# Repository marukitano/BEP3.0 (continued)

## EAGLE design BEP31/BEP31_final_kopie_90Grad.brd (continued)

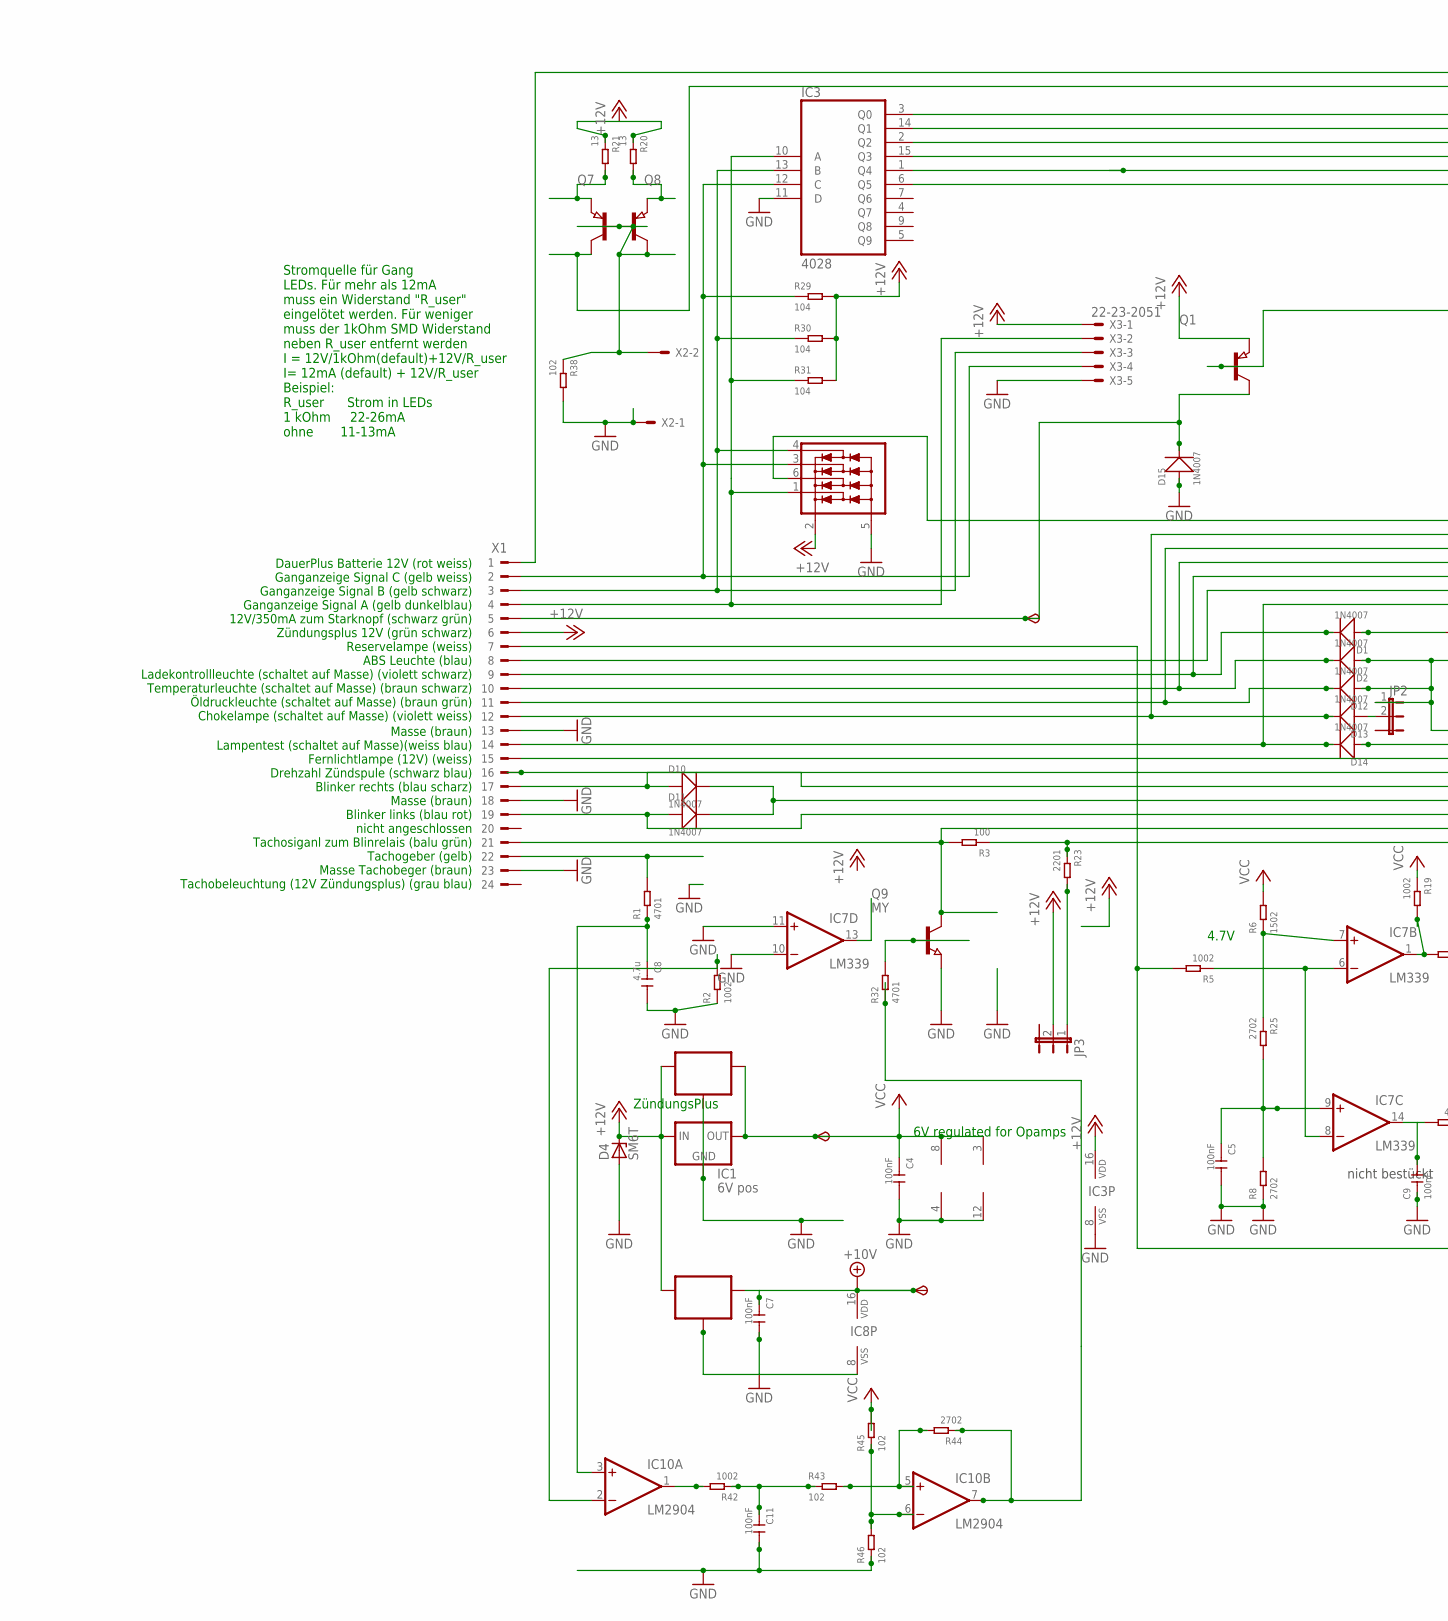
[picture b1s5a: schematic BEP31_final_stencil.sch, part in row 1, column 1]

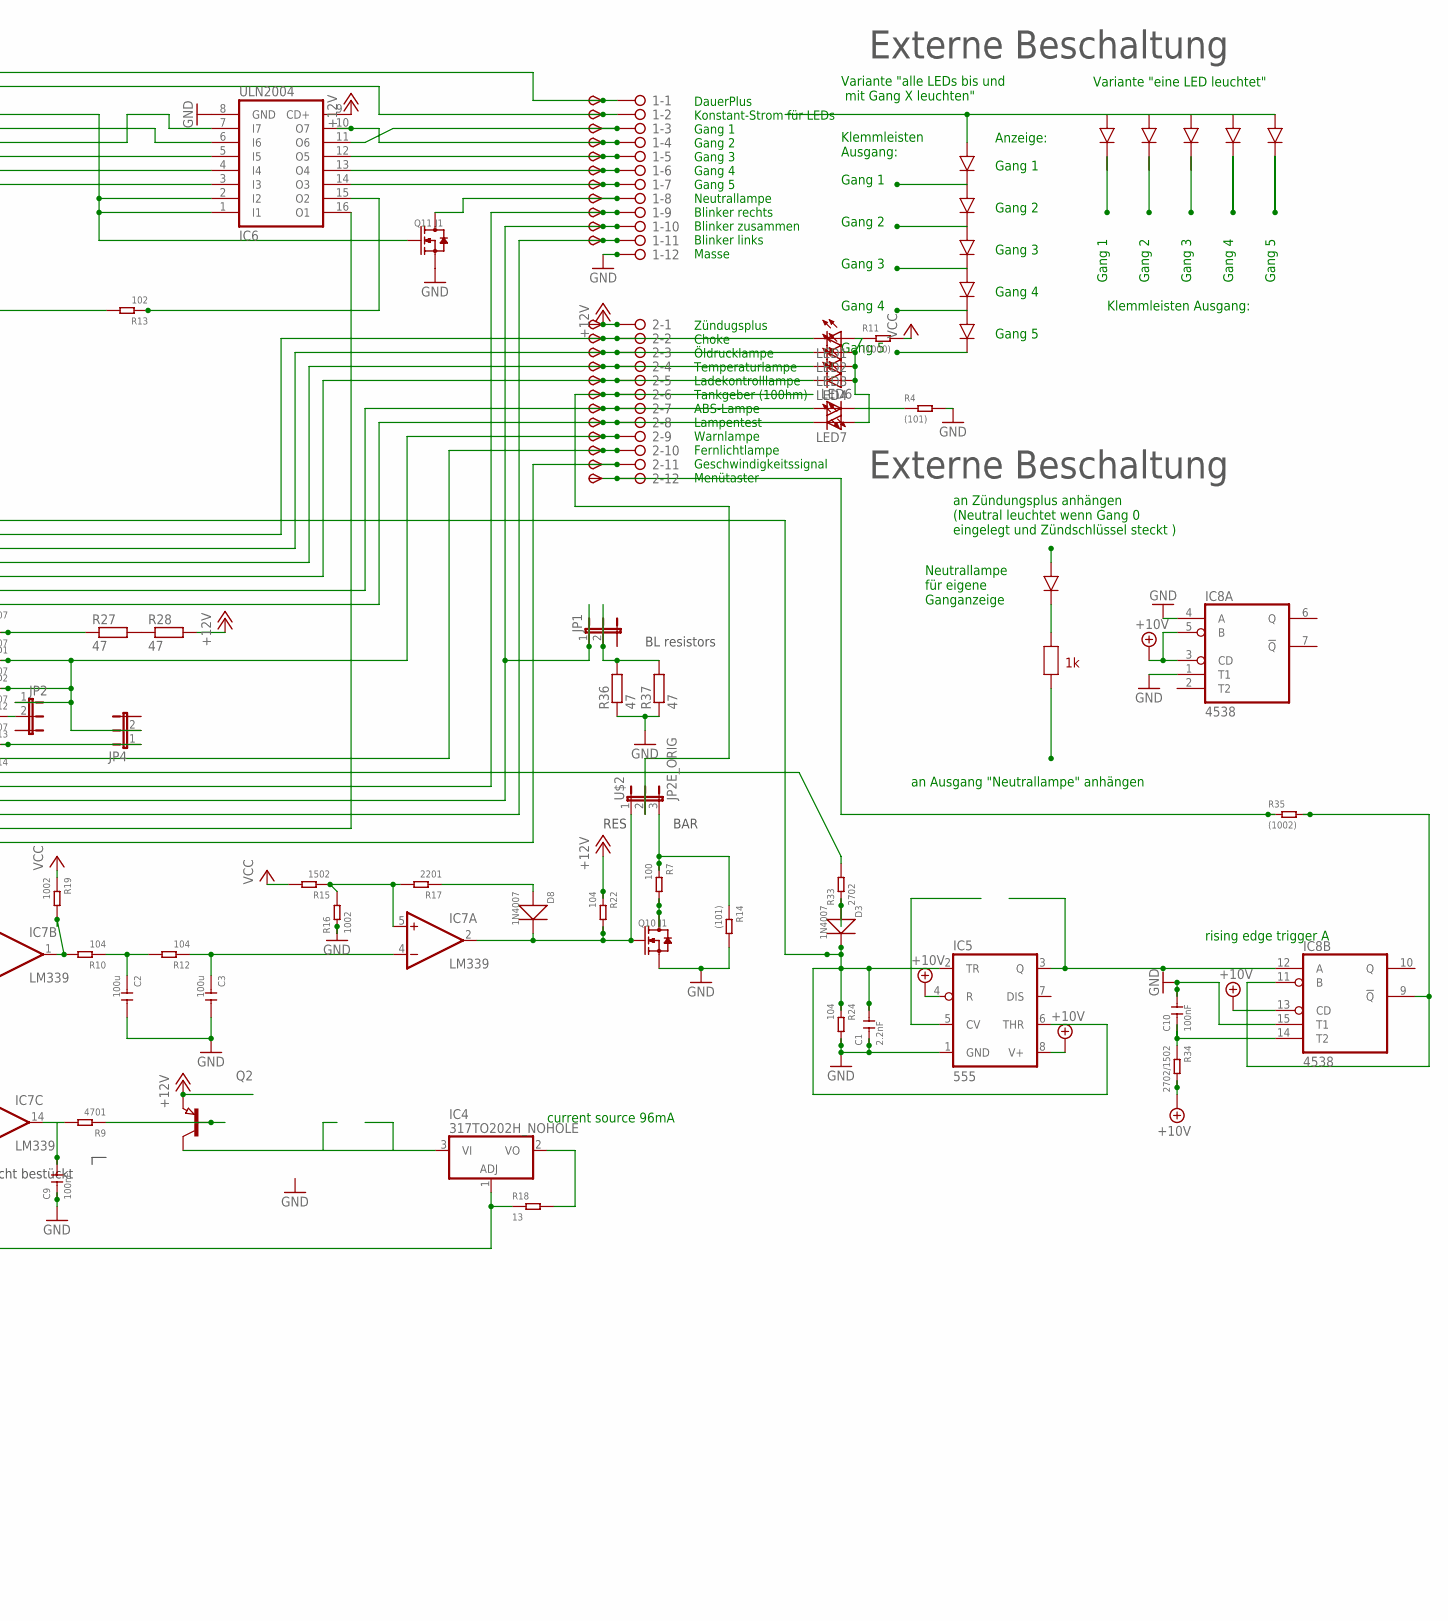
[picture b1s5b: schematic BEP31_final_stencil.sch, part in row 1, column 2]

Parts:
1, 2: 2081-1132; 12-PIN
6V, 10V: TPSB2.0; B2.0
C1: 2.2nF; C0805
C2, C3: 100u; C1206
C4, C5, C7, C9, C10, C11: 100nF; C0805
C8: 4.7u; C0805
D1, D3, D8, D10, D11, D15: 1N4007; DO-214AC
D2, D12, D13, D14: 1N4007; DO-214AC-1206MOUNT
D4: SM6T; DO214AA
IC1: 6V pos; 78LXX
IC2, IC9: 78LXXSOT89_ROUND; SOT89_ROUND
IC3: 4028; SO16
IC4: 317TO202H_NOHOLE; TO220H_NOHOLE
IC5: 555; SO08
IC6: ULN2004; SO16
IC7: LM339; SO14
IC8: 4538; SO16
IC10: LM2904; SO08
JP1, JP2, JP3, JP4: JP2EJP2_SMALLPADS; JP2_SMALLPADS
LED1, LED2, LED3, LED4, LED6, LED7: LEDLD260; LD260
Q1, Q2, Q7, Q8: PNP-TRANSISTOR_SOT89; SOT89
Q9: MY; SOT89
Q10, Q11: J1; SOT-23
R1, R9, R32: 4701; R0805
R2, R5, R16, R19, R42: 1002; R0805
R3, R7: 100; R0805
R4, R14: (101); R0805
R6, R15: 1502; R0805
R8, R25, R33, R44: 2702; R0805
R10, R12, R22, R24, R29, R30, R31: 104; R0805
R11: (1000); R0805
R13, R38, R43, R45, R46: 102; R0805
R17, R23: 2201; R0805
R18, R20, R21: 13; R1206
R27, R28, R36, R37: 47; V235/17_1MM
R34: 2702/1502; R0805
R35: (1002); R0805
START: TPSB2.0; B2.0
TP1, TP2, TP3, TP4, TP5, TP6, TP7, TP8, TP9, TP10, TP11, TP12, TP13, TP16, TP17, TP18, TP19, TP21, TP22, TP23, TP25, TP26: TPSB2.0; B2.0
TP24: TPSB1,27; B1,27
U$2: JP2E_ORIG; JP2_ORIG_SMALLPADS
U$3: NUP4304SOT457_R; SOT457R_PHILIPS
X1: CON_BMWV2; 24-PIN_V2
X2: 22-23-2021
X3: 22-23-2051

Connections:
+10V: 10V.TP, C7.1, IC5.4 (R), IC5.8 (V+), IC8.3 (CD), IC8.5 (B), IC8.13 (CD), IC8.16 (VDD), IC9.1 (OUT), R34.2
+12V: 2.1, D4.C, IC1.IN, IC2.3 (IN), IC3.16 (VDD), IC6.9 (CD+), IC9.3 (IN), JP3.2, Q1.3 (E), Q2.3 (E), R20.1, R21.1, R22.1, R28.2, R29.2, R30.2, R31.2, TP12.TP, U$3.2 (V+), X1.6, X3.1; also elsewhere on the board
+12V1: IC10.7 (OUT), R32.1, R44.1
GND: 1.12, C1.1, C2.2, C3.2, C4.2, C5.2, C7.2, C8.2, C9.1, C10.2, C11.2, D4.A, D15.1 (+), IC1.GND, IC2.2 (GND), IC2.2@1 (GND), IC3.8 (VSS), IC3.11 (D), IC5.1 (GND), IC6.8 (GND), IC7.10 (-IN), IC7.11 (+IN), IC7.12 (GND), IC8.1 (T1), IC8.4 (A), IC8.8 (VSS), IC8.15 (T1), IC9.2 (GND), IC9.2@1 (GND), IC10.4 (V-), Q9.3 (E), Q10.2 (S), Q11.2 (S), R2.1, R4.2, R8.1, R14.2, R16.1, R24.2, R36.1, R37.1, R38.2, R46.1, U$3.5 (V-), X1.13, X1.18, X1.23, X2.1, X3.5; also elsewhere on the board
unnamed: 2.9, D2.1 (+), D12.1 (+), JP2.1, JP4.2, TP24.TP
unnamed: IC3.10 (A), R31.1, U$3.1 (D1), X1.4, X3.2
unnamed: IC3.13 (B), R30.1, U$3.4 (D4), X1.3, X3.3
unnamed: 2.7, LED6.A, TP22.TP, X1.8
unnamed 8: Q8.3 (E), R21.2; also elsewhere on the board
unnamed: D8.2 (-), IC7.2 (OUT), Q10.1 (G), R22.2, U$2.1
unnamed: IC10.2 (-IN), R2.2
unnamed: R27.2, R28.1
unnamed 12: Q7.3 (E), R20.2; also elsewhere on the board
unnamed 14: D15.2 (-), Q1.2 (C), START.TP, X1.5; also elsewhere on the board
unnamed: 2.2, D13.2 (-), LED1.K (C), TP16.TP, X1.12
unnamed: 2.3, D12.2 (-), LED2.K (C), TP17.TP, X1.11
unnamed: 2.4, D2.2 (-), LED3.K (C), TP18.TP, X1.10
unnamed 18: IC4.3 (VI), Q2.2 (C); also elsewhere on the board
unnamed: IC7.6 (-IN), IC7.8 (-IN), R5.1
unnamed: IC3.12 (C), R29.1, U$3.3 (D3), X1.2, X3.4
unnamed: IC3.15 (Q3), IC6.5 (I5)
unnamed: 2.8, D14.2 (-), LED7.K (C), TP23.TP, X1.14
unnamed: 1.9, D10.1 (+), TP9.TP, X1.17
unnamed: 1.11, D11.1 (+), TP11.TP, X1.19
unnamed: IC8.9 (!Q), IC8.11 (B), R35.2
unnamed 26: R1.2, X1.22; also elsewhere on the board
unnamed: C8.1, IC10.3 (+IN), R1.1
unnamed: 1.6, IC6.13 (O4), TP6.TP
unnamed: 1.7, IC6.14 (O3), TP7.TP
unnamed: 2.11, R3.1, R23.1, TP26.TP
unnamed: 2.6, TP21.TP, U$2.2
unnamed: JP3.1, R23.2
unnamed: C5.1, IC7.9 (+IN), R8.2, R25.2
unnamed: C9.2, IC7.14 (OUT), R9.2
unnamed: C1.2, D3.2 (-), IC5.2 (TR), IC5.6 (THR), R24.1, U$3.6 (D2)
unnamed: LED6.K (C), R4.1
unnamed: IC4.1 (ADJ), R5.2, R18.1, X1.7
unnamed 39: Q2.1 (B), R9.1; also elsewhere on the board
unnamed: IC3.2 (Q2), IC6.7 (I7)
unnamed: 1.3, IC6.11 (O6), TP3.TP
unnamed: 1.5, IC6.12 (O5), TP5.TP
unnamed: LED1.A, LED2.A, LED3.A, LED4.A, LED7.A, R11.1
unnamed: R33.2, X1.16
unnamed 46: Q1.1 (B), R13.2; also elsewhere on the board
unnamed: IC3.3 (Q0), IC6.1 (I1), IC6.2 (I2), Q11.1 (G)
unnamed: C2.1, R10.1, R12.2
unnamed: C3.1, IC7.4 (-IN), R12.1
unnamed: IC7.5 (+IN), R15.1, R16.2, R17.2
unnamed: Q10.3 (D), R7.2
unnamed: D8.1 (+), R17.1
unnamed: IC3.1 (Q4), IC6.4 (I4)
unnamed: 1.8, Q11.3 (D), TP8.TP
unnamed: 2.10, TP25.TP, X1.15
unnamed: D1.1 (+), R27.1
unnamed: 2.5, D1.2 (-), LED4.K (C), TP19.TP, X1.9
unnamed: IC3.14 (Q1), IC6.6 (I6)
unnamed 59: Q7.1 (B), Q7.2 (C), Q8.1 (B), R38.1, X2.2; also elsewhere on the board
unnamed 60: 1.2, Q8.2 (C), TP2.TP; also elsewhere on the board
unnamed: IC3.6 (Q5), IC6.3 (I3)
unnamed: IC4.2 (VO), R18.2
unnamed 66: IC5.5 (CV); also elsewhere on the board
unnamed: 1.4, IC6.10 (O7), TP4.TP
unnamed: 1.1, TP1.TP, X1.1
unnamed: IC7.7 (+IN), R6.1, R25.1
unnamed 75: IC6.16 (O1), Q9.2 (C), R3.2, X1.21; also elsewhere on the board
unnamed 76: Q9.1 (B), R32.2; also elsewhere on the board
unnamed 77: IC5.3 (Q), IC8.12 (A); also elsewhere on the board
unnamed: D3.1 (+), R33.1
unnamed: IC6.15 (O2), R13.1
unnamed: C10.1, IC8.14 (T2), R34.1
unnamed: 2.12, R35.1, TP13.TP
unnamed: IC10.1 (OUT), R42.2
unnamed 83: 1.10, D10.2 (-), D11.2 (-), JP1.1, TP10.TP; also elsewhere on the board
unnamed 84: JP1.2, R36.2, R37.2; also elsewhere on the board
unnamed: D13.1 (+), JP2.2
unnamed: C11.1, R42.1, R43.1
unnamed: IC10.5 (+IN), R43.2, R44.2
unnamed: D14.1 (+), JP4.1
unnamed: R7.1, R14.1, U$2.3
unnamed: IC10.6 (-IN), R45.1, R46.2
unnamed: IC7.1 (OUT), R10.2, R19.2
VCC: 6V.TP, C4.1, IC1.OUT, IC2.1 (OUT), IC7.3 (V+), IC10.8 (V+), R6.2, R11.2, R15.2, R19.1, R45.2

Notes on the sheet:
6V regulated for Opamps
current source 96mA
ZündungsPlus
Zündugsplus Choke Öldrucklampe Temperaturlampe Ladekontrolllampe Tankgeber (100hm) ABS-Lampe Lampentest Warnlampe Fernlichtlampe Geschwindigkeitssignal Menütaster
DauerPlus Konstant-Strom für LEDs Gang 1 Gang 2 Gang 3 Gang 4 Gang 5 Neutrallampe Blinker rechts Blinker zusammen Blinker links Masse
DauerPlus Batterie 12V (rot weiss) Ganganzeige Signal C (gelb weiss) Ganganzeige Signal B (gelb schwarz) Ganganzeige Signal A (gelb dunkelblau) 12V/350mA zum Starknopf (schwarz grün) Zündungsplus 12V (grün schwarz) Reservelampe (weiss) ABS Leuchte (blau) Ladekontrollleuchte (schaltet auf Masse) (vi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
Masse (braun) Lampentest (schaltet auf Masse)(weiss blau) Fernlichtlampe (12V) (weiss) Drehzahl Zündspule (schwarz blau) Blinker rechts (blau scharz) Masse (braun) Blinker links (blau rot) nicht angeschlossen Tachosiganl zum Blinrelais (balu grün) Tachogeber (gelb) Masse Tachobeger (braun) Tachobel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
4.7V
Stromquelle für Gang LEDs. Für mehr als 12mA muss ein Widerstand "R_user" eingelötet werden. Für weniger muss der 1kOhm SMD Widerstand neben R_user entfernt werden I = 12V/1kOhm(default)+12V/R_user I= 12mA (default) + 12V/R_user Beispiel: R_user Strom in LEDs 1 kOhm 22-26mA ohne 11-13mA
Gang 1
Gang 2
Gang 3
Gang 4
Gang 5
Variante "eine LED leuchtet"
Variante "alle LEDs bis und mit Gang X leuchten"
Klemmleisten Ausgang:
Klemmleisten Ausgang:
an Zündungsplus anhängen (Neutral leuchtet wenn Gang 0 eingelegt und Zündschlüssel steckt )
an Ausgang "Neutrallampe" anhängen
Neutrallampe für eigene Ganganzeige
Externe Beschaltung
Anzeige:
nicht bestückt
rising edge trigger A
BAR
RES
BL resistors

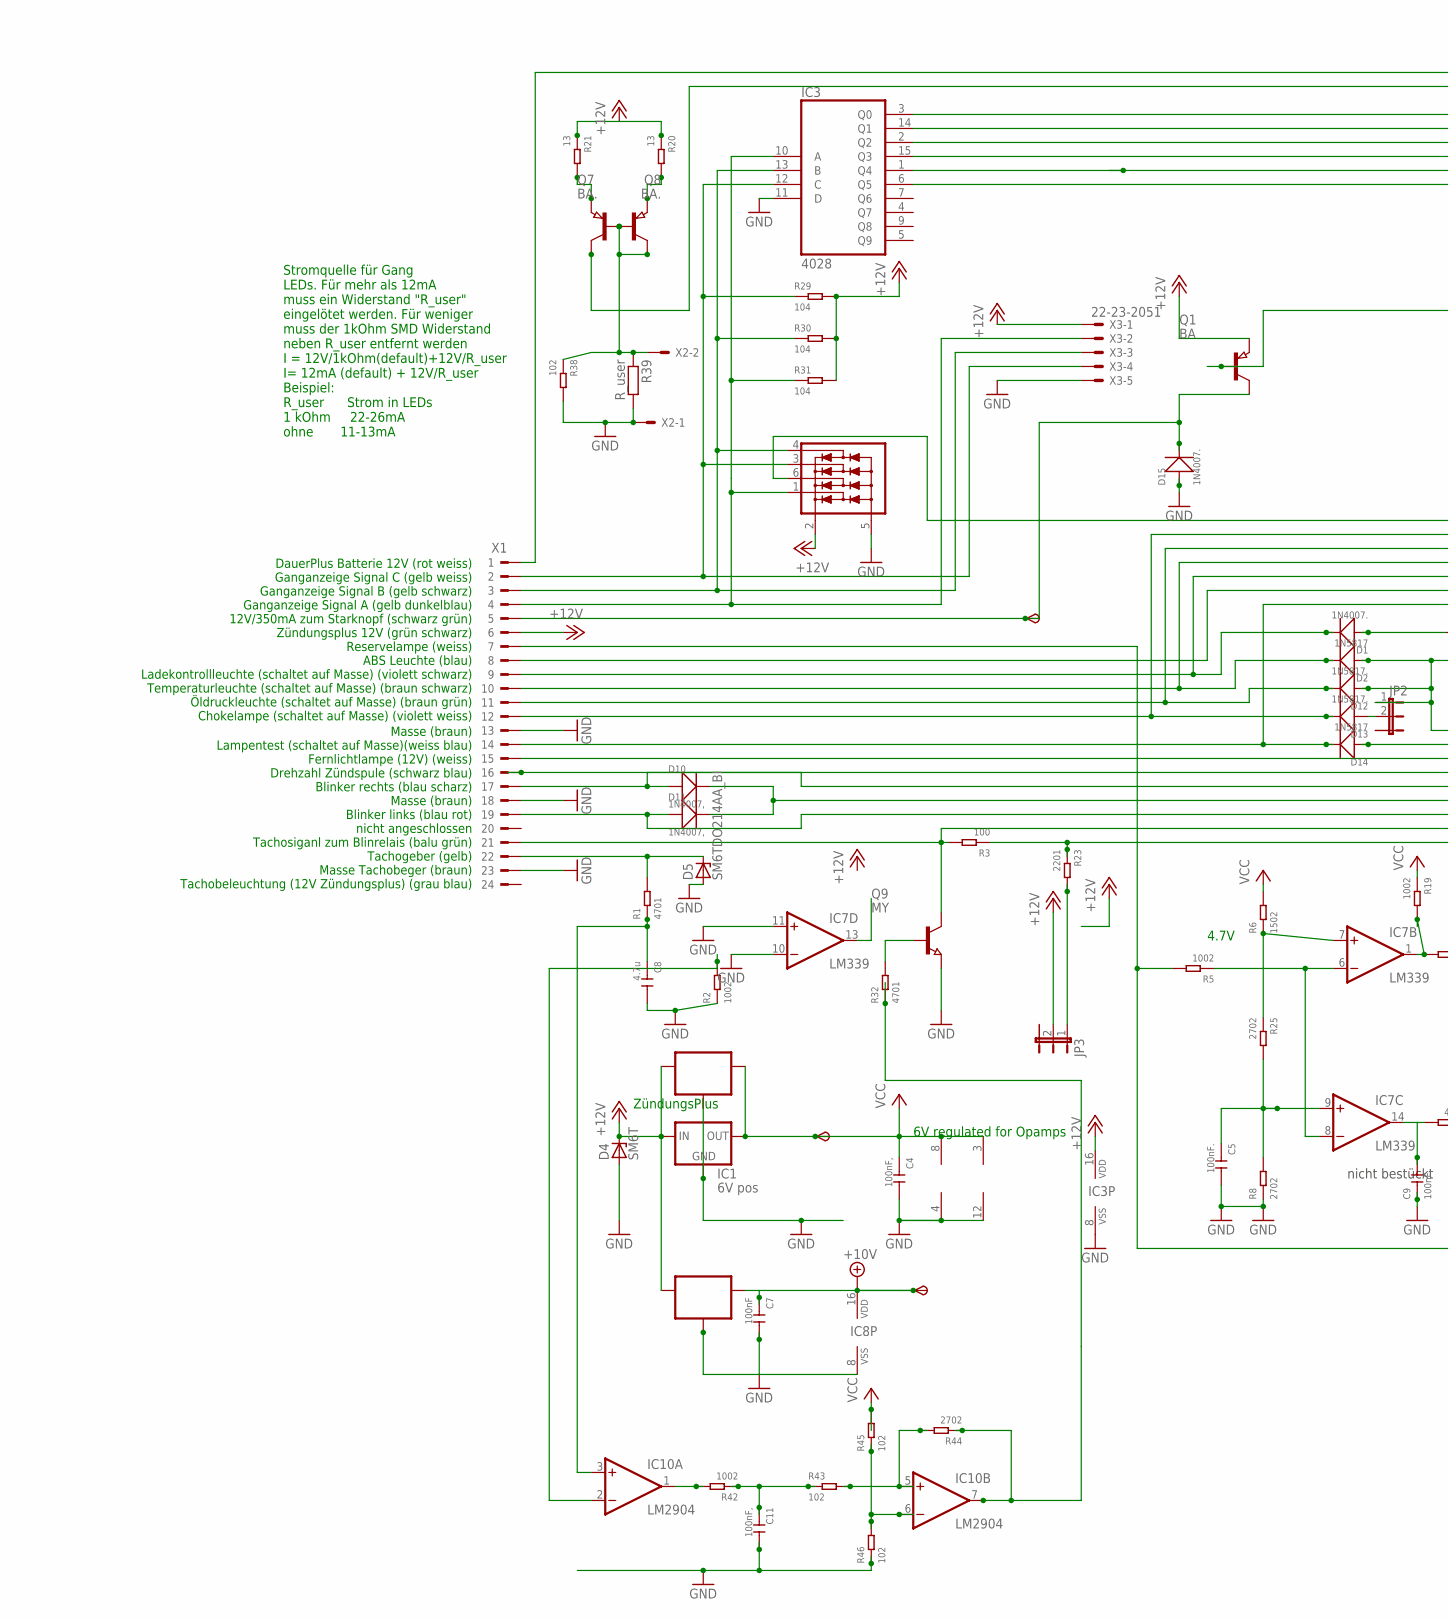
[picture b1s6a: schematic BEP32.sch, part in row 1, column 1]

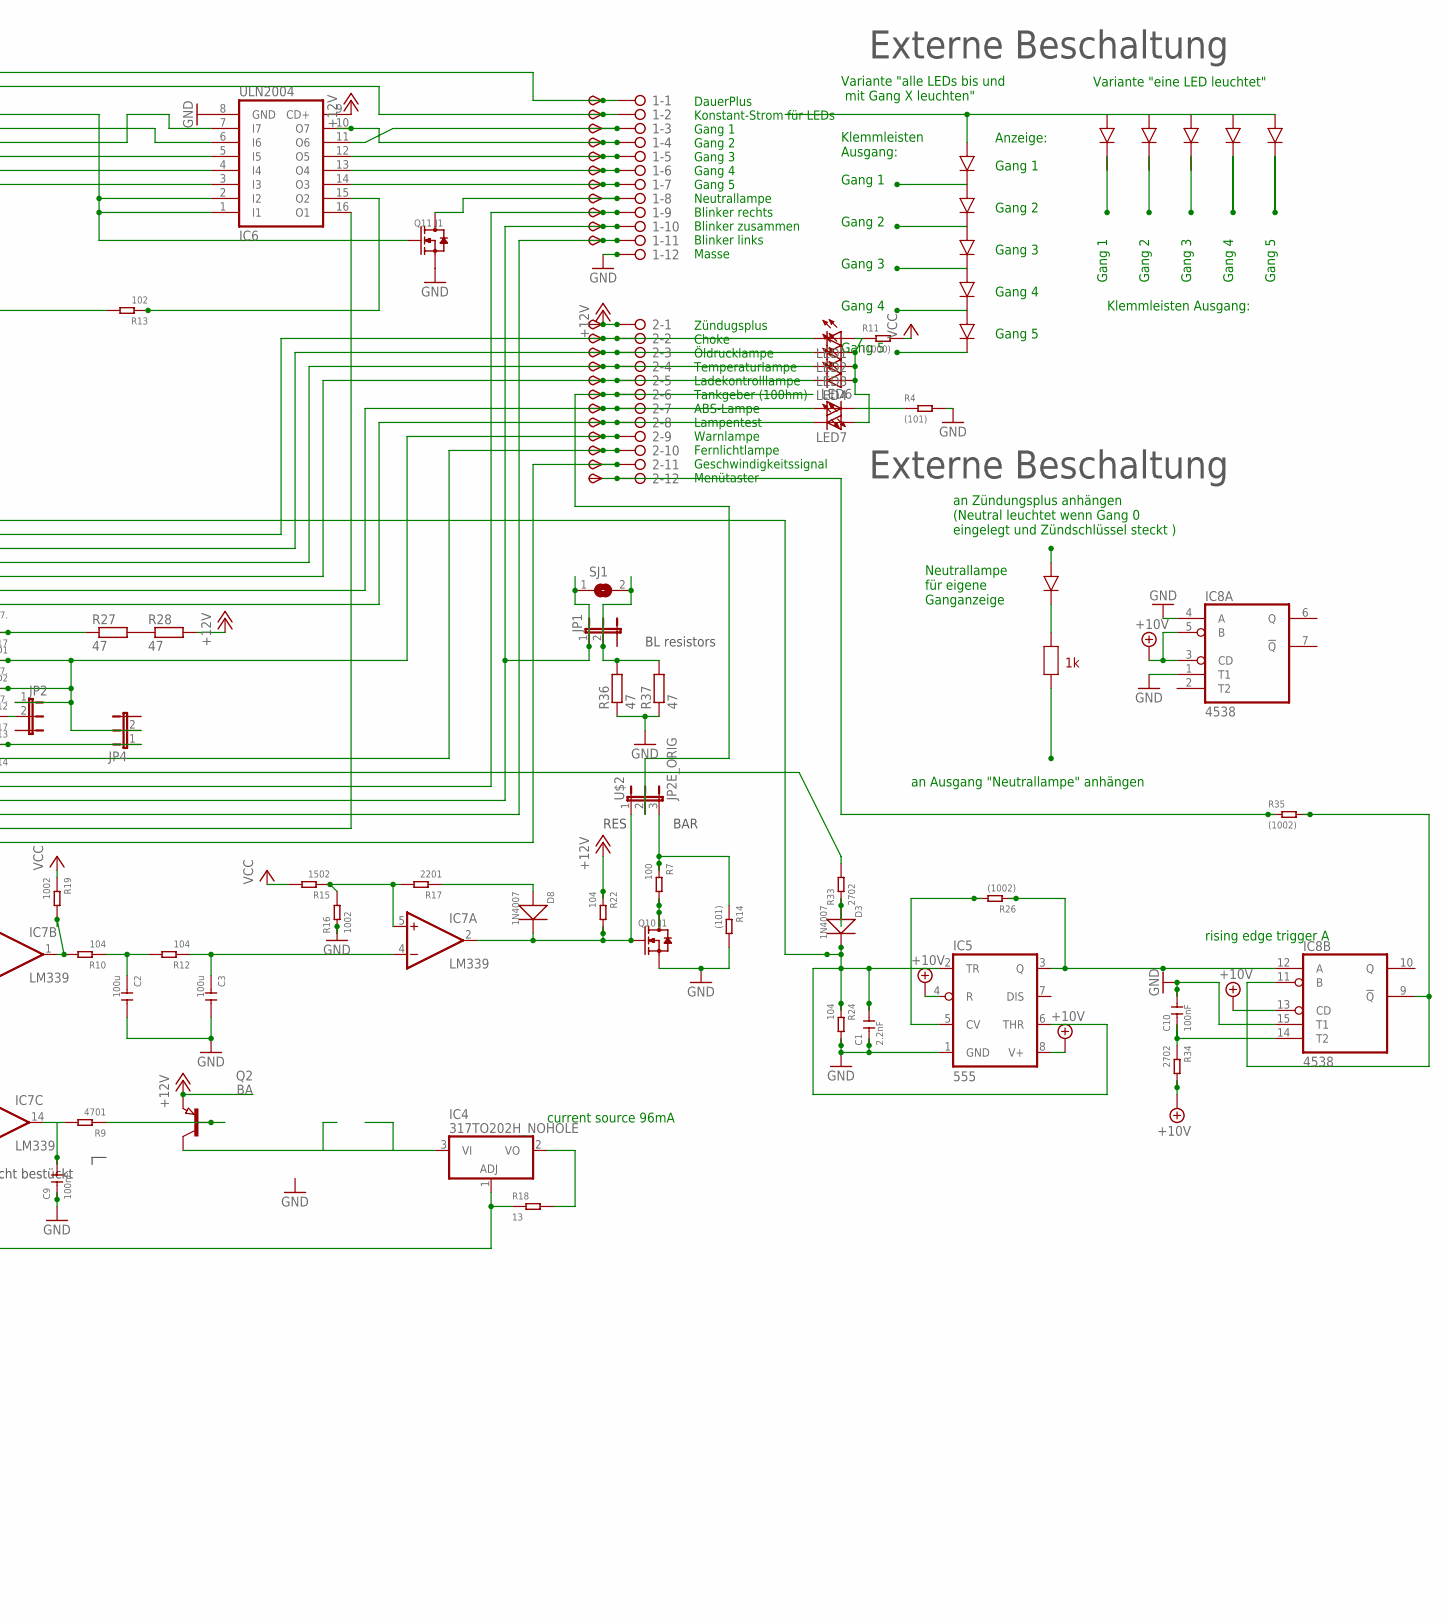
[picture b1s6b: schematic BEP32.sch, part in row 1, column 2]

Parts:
1, 2: 2081-1132; 12-PIN
6V, 10V: TPSB2.0; B2.0
C1: 2.2nF; C0805
C2, C3: 100u; C1206
C4, C11: 100nF,; C0805
C5, C9: 100nF.; C0805
C7, C10: 100nF; C0805
C8: 4.7u; C0805
D1, D15: 1N4007.; DO-214AC
D2, D14: 1N5817; DO-214AC_SLIM
D3, D8: 1N4007; DO-214AC
D4: SM6T; DO214AA
D5: SM6TDO214AA_BI; DO214AA_BI
D10, D11: 1N4007,; DO-214AC
D12, D13: 1N5817.; DO-214AC_SLIM
IC1: 6V pos; 78LXX
IC2: 78L06; SOT89_ROUND
IC3: 4028; SO16
IC4: 317TO202H_NOHOLE; TO220H_NOHOLE
IC5: 555; SO08
IC6: ULN2004; SO16
IC7: LM339; SO14
IC8: 4538; SO16
IC9: 78L10; SOT89_ROUND
IC10: LM2904; SO08
JP1, JP2, JP3, JP4: JP2EJP2_SMALLPADS; JP2_SMALLPADS
LED1, LED2, LED3, LED4, LED6, LED7: LEDLD260; LD260
Q1, Q2: BA; SOT89
Q7, Q8: BA.; SOT89
Q9: MY; SOT89
Q10, Q11: J1; SOT-23
R1, R9, R32: 4701; R0805
R2, R5, R16, R19, R42: 1002; R0805
R3, R7: 100; R0805
R4, R14: (101); R0805
R6, R15: 1502; R0805
R8, R25, R33, R34, R44: 2702; R0805
R10, R12, R22, R24, R29, R30, R31: 104; R0805
R11: (1000); R0805
R13, R38, R43, R45, R46: 102; R0805
R17, R23: 2201; R0805
R18, R20, R21: 13; R1206
R26, R35: (1002); R0805
R27, R28, R36, R37: 47; V235/17_1MM
R39: R_user; R0805
SJ1: SJ
START: TPSB2.0; B2.0
TP1, TP2, TP3, TP4, TP5, TP6, TP7, TP8, TP9, TP10, TP11, TP12, TP13, TP16, TP17, TP18, TP19, TP21, TP22, TP23, TP25, TP26: TPSB2.0; B2.0
TP24: TPSB1,27; B1,27
U$2: JP2E_ORIG; JP2_ORIG_SMALLPADS
U$3: NUP4304SOT457_R; SOT457R_PHILIPS
X1: CON_BMWV2; 24-PIN_V2
X2: 22-23-2021
X3: 22-23-2051

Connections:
+10V: 10V.TP, C7.1, IC5.4 (R), IC5.8 (V+), IC8.3 (CD), IC8.5 (B), IC8.13 (CD), IC8.16 (VDD), IC9.1 (OUT), R34.2
+12V: 2.1, D4.C, IC1.IN, IC2.3 (IN), IC3.16 (VDD), IC6.9 (CD+), IC9.3 (IN), JP3.2, Q1.3 (E), Q2.3 (E), R20.1, R21.1, R22.1, R28.2, R29.2, R30.2, R31.2, TP12.TP, U$3.2 (V+), X1.6, X3.1; also elsewhere on the board
+12V1: IC10.7 (OUT), R32.1, R44.1
GND: 1.12, C1.1, C2.2, C3.2, C4.2, C5.2, C7.2, C8.2, C9.1, C10.2, C11.2, D4.A, D5.A, D15.1 (+), IC1.GND, IC2.2 (GND), IC2.2@1 (GND), IC3.8 (VSS), IC3.11 (D), IC5.1 (GND), IC6.8 (GND), IC7.10 (-IN), IC7.11 (+IN), IC7.12 (GND), IC8.1 (T1), IC8.4 (A), IC8.8 (VSS), IC8.15 (T1), IC9.2 (GND), IC9.2@1 (GND), IC10.4 (V-), Q9.3 (E), Q10.2 (S), Q11.2 (S), R2.1, R4.2, R8.1, R14.2, R16.1, R24.2, R36.1, R37.1, R38.2, R39.2, R46.1, U$3.5 (V-), X1.13, X1.18, X1.23, X2.1, X3.5; also elsewhere on the board
unnamed: 2.9, D2.1 (+), D12.1 (+), JP2.1, JP4.2, TP24.TP
unnamed: IC3.10 (A), R31.1, U$3.1 (D1), X1.4, X3.2
unnamed: IC3.13 (B), R30.1, U$3.4 (D4), X1.3, X3.3
unnamed: 2.7, LED6.A, TP22.TP, X1.8
unnamed 8: Q8.3 (E), R21.2; also elsewhere on the board
unnamed: D8.2 (-), IC7.2 (OUT), Q10.1 (G), R22.2, U$2.1
unnamed: IC10.2 (-IN), R2.2
unnamed: R27.2, R28.1
unnamed 12: Q7.3 (E), R20.2; also elsewhere on the board
unnamed 14: D15.2 (-), Q1.2 (C), START.TP, X1.5; also elsewhere on the board
unnamed: 2.2, D13.2 (-), LED1.K (C), TP16.TP, X1.12
unnamed: 2.3, D12.2 (-), LED2.K (C), TP17.TP, X1.11
unnamed: 2.4, D2.2 (-), LED3.K (C), TP18.TP, X1.10
unnamed 18: IC4.3 (VI), Q2.2 (C); also elsewhere on the board
unnamed: IC7.6 (-IN), IC7.8 (-IN), R5.1
unnamed: IC3.12 (C), R29.1, U$3.3 (D3), X1.2, X3.4
unnamed: IC3.15 (Q3), IC6.5 (I5)
unnamed: 2.8, D14.2 (-), LED7.K (C), TP23.TP, X1.14
unnamed: 1.9, D10.1 (+), TP9.TP, X1.17
unnamed: 1.11, D11.1 (+), TP11.TP, X1.19
unnamed: IC8.9 (!Q), IC8.11 (B), R35.2
unnamed: D5.C, R1.2, X1.22
unnamed: C8.1, IC10.3 (+IN), R1.1
unnamed: 1.6, IC6.13 (O4), TP6.TP
unnamed: 1.7, IC6.14 (O3), TP7.TP
unnamed: 2.11, R3.1, R23.1, TP26.TP
unnamed: 2.6, TP21.TP, U$2.2
unnamed: JP3.1, R23.2
unnamed: C5.1, IC7.9 (+IN), R8.2, R25.2
unnamed: C9.2, IC7.14 (OUT), R9.2
unnamed: C1.2, D3.2 (-), IC5.2 (TR), IC5.6 (THR), R24.1, U$3.6 (D2)
unnamed: LED6.K (C), R4.1
unnamed: IC4.1 (ADJ), R5.2, R18.1, X1.7
unnamed 39: Q2.1 (B), R9.1; also elsewhere on the board
unnamed: IC3.2 (Q2), IC6.7 (I7)
unnamed: 1.3, IC6.11 (O6), TP3.TP
unnamed: 1.5, IC6.12 (O5), TP5.TP
unnamed: LED1.A, LED2.A, LED3.A, LED4.A, LED7.A, R11.1
unnamed: R33.2, X1.16
unnamed 46: Q1.1 (B), R13.2; also elsewhere on the board
unnamed: IC3.3 (Q0), IC6.1 (I1), IC6.2 (I2), Q11.1 (G)
unnamed: C2.1, R10.1, R12.2
unnamed: C3.1, IC7.4 (-IN), R12.1
unnamed: IC7.5 (+IN), R15.1, R16.2, R17.2
unnamed: Q10.3 (D), R7.2
unnamed: D8.1 (+), R17.1
unnamed: IC3.1 (Q4), IC6.4 (I4)
unnamed: 1.8, Q11.3 (D), TP8.TP
unnamed: 2.10, TP25.TP, X1.15
unnamed: D1.1 (+), R27.1
unnamed: 2.5, D1.2 (-), LED4.K (C), TP19.TP, X1.9
unnamed: IC3.14 (Q1), IC6.6 (I6)
unnamed 59: Q7.1 (B), Q7.2 (C), Q8.1 (B), R38.1, R39.1, X2.2; also elsewhere on the board
unnamed 60: 1.2, Q8.2 (C), TP2.TP; also elsewhere on the board
unnamed: IC3.6 (Q5), IC6.3 (I3)
unnamed: IC4.2 (VO), R18.2
unnamed: IC5.5 (CV), R26.2
unnamed: 1.4, IC6.10 (O7), TP4.TP
unnamed: 1.1, TP1.TP, X1.1
unnamed: IC7.7 (+IN), R6.1, R25.1
unnamed 75: IC6.16 (O1), Q9.2 (C), R3.2, X1.21; also elsewhere on the board
unnamed 76: Q9.1 (B), R32.2; also elsewhere on the board
unnamed: IC5.3 (Q), IC8.12 (A), R26.1
unnamed: D3.1 (+), R33.1
unnamed: IC6.15 (O2), R13.1
unnamed: C10.1, IC8.14 (T2), R34.1
unnamed: 2.12, R35.1, TP13.TP
unnamed: IC10.1 (OUT), R42.2
unnamed: 1.10, D10.2 (-), D11.2 (-), JP1.1, SJ1.1, TP10.TP
unnamed: JP1.2, R36.2, R37.2, SJ1.2
unnamed: D13.1 (+), JP2.2
unnamed: C11.1, R42.1, R43.1
unnamed: IC10.5 (+IN), R43.2, R44.2
unnamed: D14.1 (+), JP4.1
unnamed: R7.1, R14.1, U$2.3
unnamed: IC10.6 (-IN), R45.1, R46.2
unnamed: IC7.1 (OUT), R10.2, R19.2
VCC: 6V.TP, C4.1, IC1.OUT, IC2.1 (OUT), IC7.3 (V+), IC10.8 (V+), R6.2, R11.2, R15.2, R19.1, R45.2

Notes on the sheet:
6V regulated for Opamps
current source 96mA
ZündungsPlus
Zündugsplus Choke Öldrucklampe Temperaturlampe Ladekontrolllampe Tankgeber (100hm) ABS-Lampe Lampentest Warnlampe Fernlichtlampe Geschwindigkeitssignal Menütaster
DauerPlus Konstant-Strom für LEDs Gang 1 Gang 2 Gang 3 Gang 4 Gang 5 Neutrallampe Blinker rechts Blinker zusammen Blinker links Masse
DauerPlus Batterie 12V (rot weiss) Ganganzeige Signal C (gelb weiss) Ganganzeige Signal B (gelb schwarz) Ganganzeige Signal A (gelb dunkelblau) 12V/350mA zum Starknopf (schwarz grün) Zündungsplus 12V (grün schwarz) Reservelampe (weiss) ABS Leuchte (blau) Ladekontrollleuchte (schaltet auf Masse) (vi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
Masse (braun) Lampentest (schaltet auf Masse)(weiss blau) Fernlichtlampe (12V) (weiss) Drehzahl Zündspule (schwarz blau) Blinker rechts (blau scharz) Masse (braun) Blinker links (blau rot) nicht angeschlossen Tachosiganl zum Blinrelais (balu grün) Tachogeber (gelb) Masse Tachobeger (braun) Tachobel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
4.7V
Stromquelle für Gang LEDs. Für mehr als 12mA muss ein Widerstand "R_user" eingelötet werden. Für weniger muss der 1kOhm SMD Widerstand neben R_user entfernt werden I = 12V/1kOhm(default)+12V/R_user I= 12mA (default) + 12V/R_user Beispiel: R_user Strom in LEDs 1 kOhm 22-26mA ohne 11-13mA
Gang 1
Gang 2
Gang 3
Gang 4
Gang 5
Variante "eine LED leuchtet"
Variante "alle LEDs bis und mit Gang X leuchten"
Klemmleisten Ausgang:
Klemmleisten Ausgang:
an Zündungsplus anhängen (Neutral leuchtet wenn Gang 0 eingelegt und Zündschlüssel steckt )
an Ausgang "Neutrallampe" anhängen
Neutrallampe für eigene Ganganzeige
Externe Beschaltung
Anzeige:
nicht bestückt
rising edge trigger A
BAR
RES
BL resistors

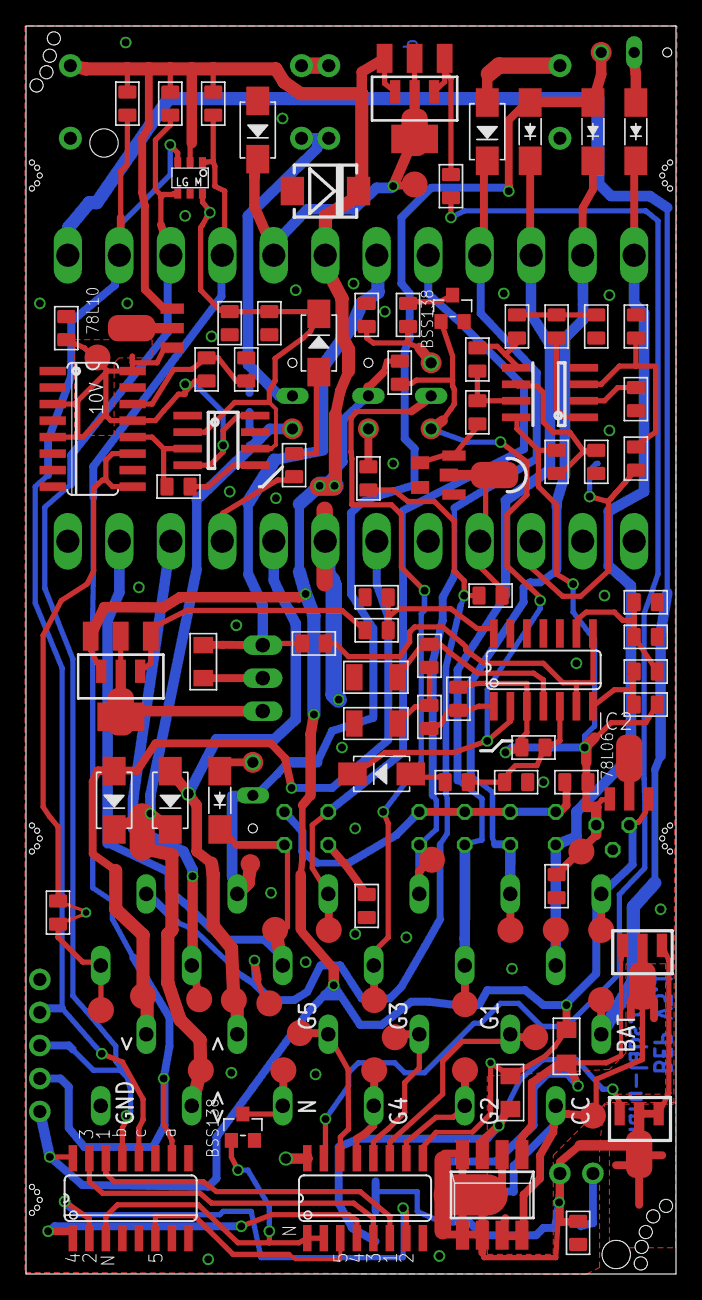
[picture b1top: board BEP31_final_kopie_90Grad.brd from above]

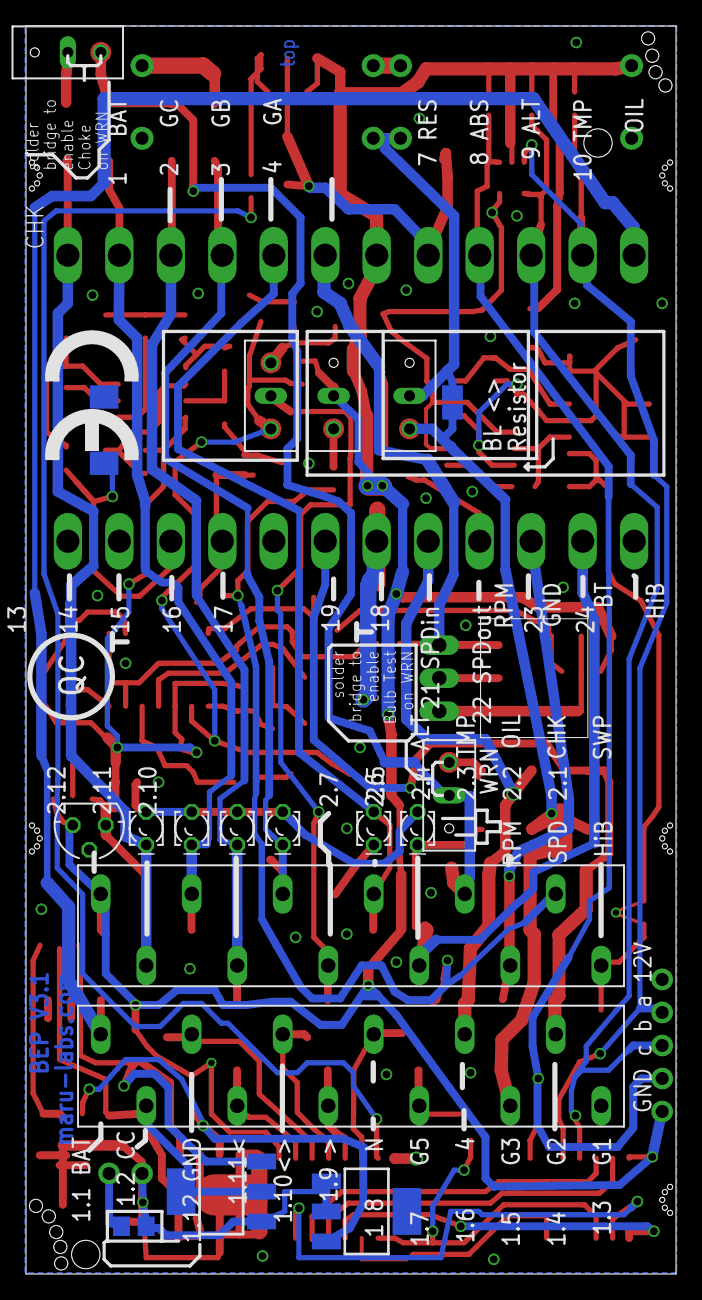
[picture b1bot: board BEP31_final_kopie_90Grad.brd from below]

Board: 2 copper layers, 50.0 x 96.0 mm, 136 parts (28 on the bottom side), 82 nets.

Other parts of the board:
FID1: FID1; ROUND_1.5MM_TPLACE
FID2: FID2; ROUND_1.5MM_TPLACE
U$1: CE_10.00

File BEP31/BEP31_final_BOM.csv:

"Qty";"Value";"Device";"Package";"Parts";"Description";"MF";"MPN";"OC_FARNELL";"OC_NEWARK";"TP";"TP_SIGNAL_NAME";"VALUE";
"2";"";"2081-1132";"12-PIN";"1, 2";"WAGO SREW CLAMP";"";"";"";"";"";"";"";
"2";"";"78LXXSOT89_ROUND";"SOT89_ROUND";"IC2, IC9";"";"";"";"";"";"";"";"";
"1";"";"CON_BMWV2";"24-PIN_V2";"X1";"BMW CONNECTOR";"";"";"";"";"";"";"";
"4";"";"JP2EJP2_SMALLPADS";"JP2_SMALLPADS";"JP1, JP2, JP3, JP4";"JUMPER";"";"";"";"";"";"";"";
"6";"";"LEDLD260";"LD260";"LED1, LED2, LED3, LED4, LED6, LED7";"LED";"";"";"";"";"";"";"";
"4";"";"PNP-TRANSISTOR_SOT89";"SOT89";"Q1, Q2, Q7, Q8";"PNP TRANSISTOR";"";"";"";"";"";"";"";
"1";"(1000)";"SMD-RES-100R-5%-1/8W(0805)";"R0805";"R11";"301010319";"";"RC0805JR-07100RL";"";"";"";"";"100R";
"1";"(1002)";"SMD-RES-4.7K-5%-1/8W(0805)";"R0805";"R35";"301010306";"";"RC0805JR-074K7L";"";"";"";"";"4.7K";
"1";"(101)";"SMD-RES-100R-5%-1/8W(0805)";"R0805";"R4";"301010319";"";"RC0805JR-07100RL";"";"";"";"";"100R";
"1";"(101)";"SMD-RES-2.2K-5%-1/8W(0805)";"R0805";"R14";"301010333";"";"RC0805JR-072K2L";"";"";"";"";"2.2K";
"1";"100";"SMD-RES-2.2K-5%-1/8W(0805)";"R0805";"R7";"301010333";"";"RC0805JR-072K2L";"";"";"";"";"2.2K";
"1";"100";"SMD-RES-220R-5%-1/8W(0805)";"R0805";"R3";"301010315";"";"RC0805JR-07220RL";"";"";"";"";"220R";
"5";"1002";"SMD-RES-10K-1%-1/8W(0805)";"R0805";"R2, R5, R16, R19, R42";"301010361";"";"RC0805FR-0710KL";"";"";"";"";"10K";
"6";"100nF";"CERAMIC-100NF-50V-10%-X7R(0805)";"C0805";"C4, C5, C7, C9, C10, C11";"302010165";"";"CC0805KRX7R9BB104";"";"";"";"";"100nf";
"2";"100u";"CERAMIC-100UF-6.3V-20%-X5R(1206)";"C1206";"C2, C3";"302010183";"";"GRM31CR60J107ME39L";"";"";"";"";"100uf";
"5";"102";"SMD-RES-1K-5%-1/8W(0805)";"R0805";"R13, R38, R43, R45, R46";"301010311";"";"RC0805JR-071KL";"";"";"";"";"1K";
"7";"104";"SMD-RES-10K-1%-1/8W(0805)";"R0805";"R10, R12, R22, R24, R29, R30, R31";"301010361";"";"RC0805FR-0710KL";"";"";"";"";"10K";
"3";"13";"SMD-RES-13R-5%-1/4W(1206)";"R1206";"R18, R20, R21";"301010405";"";"RC1206JR-0713RL";"";"";"";"";"13R";
"2";"1502";"SMD-RES-10K-1%-1/8W(0805)";"R0805";"R6, R15";"301010361";"";"RC0805FR-0710KL";"";"";"";"";"10K";
"6";"1N4007";"DIODE-GEN-PURPOSE-1KV-1A(DO-214AC)";"DO-214AC";"D1, D3, D8, D10, D11, D15";"304010013";"";"1N4007";"";"";"";"";"1N4007";
"4";"1N4007";"DIODE-GEN-PURPOSE-1KV-1A(DO-214AC)DO-214AC/1206";"DO-214AC-1206MOUNT";"D2, D12, D13, D14";"304010013";"";"";"";"";"";"";"";
"1";"2.2nF";"CERAMIC-100NF-50V-10%-X7R(0805)";"C0805";"C1";"302010165";"";"CC0805KRX7R9BB104";"";"";"";"";"100nf";
"1";"22-23-2021";"22-23-2021";"22-23-2021";"X2";".100" (2.54mm) Center Header - 2 Pin";"MOLEX";"22-23-2021";"1462926";"25C3832";"";"";"";
"1";"22-23-2051";"22-23-2051";"22-23-2051";"X3";".100" (2.54mm) Center Header - 5 Pin";"MOLEX";"22-23-2051";"1462952";"38C9178";"";"";"";
"2";"2201";"SMD-RES-2.2K-5%-1/8W(0805)";"R0805";"R17, R23";"301010333";"";"RC0805JR-072K2L";"";"";"";"";"2.2K";
"1";"2702";"SMD-RES-10K-1%-1/8W(0805)";"R0805";"R33";"301010361";"";"RC0805FR-0710KL";"";"";"";"";"10K";
"3";"2702";"SMD-RES-4.7K-5%-1/8W(0805)";"R0805";"R8, R25, R44";"301010306";"";"RC0805JR-074K7L";"";"";"";"";"4.7K";
"1";"2702/1502";"SMD-RES-4.7K-5%-1/8W(0805)";"R0805";"R34";"301010306";"";"RC0805JR-074K7L";"";"";"";"";"4.7K";
"1";"317TO202H_NOHOLE";"317TO202H_NOHOLE";"TO220H_NOHOLE";"IC4";"Positive VOLTAGE REGULATOR";"";"";"";"";"";"";"";
"1";"4.7u";"CERAMIC-4.7UF-25V-10%-X5R(0805)";"C0805";"C8";"302010146";"";"CC0805KKX5R8BB475";"";"";"";"";"4.7uf";
"1";"4028";"4028D";"SO16";"IC3";"BCD to decimal DECODER";"";"";"";"";"";"";"";
"1";"4538";"4538D";"SO16";"IC8";"Dual precision monostable MULTIVIBRATOR";"";"";"";"";"";"";"";
"4";"47";"R-EU_V235/17_1MM";"V235/17_1MM";"R27, R28, R36, R37";"RESISTOR, European symbol";"";"";"";"";"";"";"";
"3";"4701";"SMD-RES-4.7K-5%-1/8W(0805)";"R0805";"R1, R9, R32";"301010306";"";"RC0805JR-074K7L";"";"";"";"";"4.7K";
"1";"555";"NE555D";"SO08";"IC5";"TIMER";"";"";"";"";"";"";"";
"1";"6V pos";"78LXX";"78LXX";"IC1";"VOLTAGE REGULATOR";"";"";"";"";"";"";"";
"2";"J1";"SMD-MOSFET-N-CH-50V-200MA-BSS138W-7-F(SOT-23)";"SOT-23";"Q10, Q11";"305030000";"";"BSS138W-7-F";"";"";"";"";"BSS138W-7-F";
"1";"JP2E_ORIG";"JP2E_ORIG";"JP2_ORIG_SMALLPADS";"U$2";"";"";"";"";"";"";"";"";
"1";"LM2904";"LM358D";"SO08";"IC10";"OP AMP also LM158; LM258; LM2904";"";"";"";"";"";"";"";
"1";"LM339";"LM339D";"SO14";"IC7";"Low Power Low Offset Voltage Quad Comparators";"";"";"";"";"";"";"";
"1";"MY";"NPN-TRANSISTOR_SOT89";"SOT89";"Q9";"NPN TRANSISTOR";"";"";"";"";"";"";"";
"1";"NUP4304SOT457_R";"NUP4304SOT457_R";"SOT457R_PHILIPS";"U$3";"";"";"";"";"";"";"";"";
"1";"SM6T";"SM6T";"DO214AA";"D4";"Z DIODE";"";"";"";"";"";"";"";
"1";"TPSB1,27";"TPSB1,27";"B1,27";"TP24";"TEST PIN";"";"";"";"";"";"";"";
"25";"TPSB2.0";"TPSB2.0";"B2.0";"6V, 10V, START, TP1, TP2, TP3, TP4, TP5, TP6, TP7, TP8, TP9, TP10, TP11, TP12, TP13, TP16, TP17, TP18, TP19, TP21, TP22, TP23, TP25, TP26";"TEST PIN";"";"";"";"";"";"";"";
"1";"ULN2004";"ULN2004AD";"SO16";"IC6";"DRIVER ARRAY";"";"";"";"";"";"";"";
